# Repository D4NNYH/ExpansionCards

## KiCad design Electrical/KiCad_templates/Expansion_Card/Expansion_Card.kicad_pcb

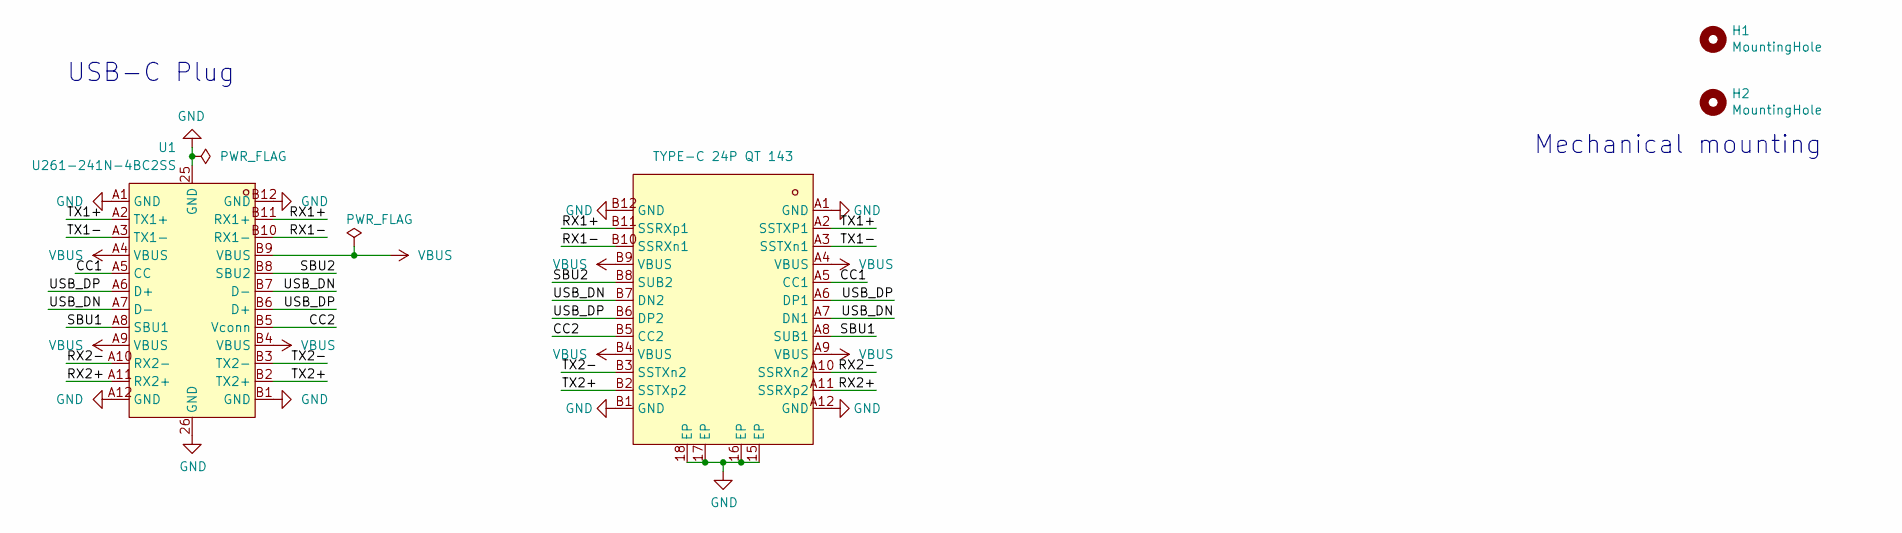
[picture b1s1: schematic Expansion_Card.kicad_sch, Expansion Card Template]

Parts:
H1, H2: MountingHole; MountingHole_2.2mm_M2
U1: U261-241N-4BC2SS; USB-C-SMD_XKB_U261-24XN-4BC2SS; MPN U261-241N-4BC2SS; LCSC Part C2938597
USB1: TYPE-C 24P QT 143; TYPE-C-SMD_C9900025773; MPN TYPE-C 24P QT 143; LCSC Part C5156605

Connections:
/CC1: U1.A5 (CC), USB1.A5 (CC1)
/CC2: U1.B5 (Vconn), USB1.B5 (CC2)
/RX1+: U1.B11 (RX1+), USB1.B11 (SSRXp1)
/RX1-: U1.B10 (RX1-), USB1.B10 (SSRXn1)
/RX2+: U1.A11 (RX2+), USB1.A11 (SSRXp2)
/RX2-: U1.A10 (RX2-), USB1.A10 (SSRXn2)
/SBU1: U1.A8 (SBU1), USB1.A8 (SUB1)
/SBU2: U1.B8 (SBU2), USB1.B8 (SUB2)
/TX1+: U1.A2 (TX1+), USB1.A2 (SSTXP1)
/TX1-: U1.A3 (TX1-), USB1.A3 (SSTXn1)
/TX2+: U1.B2 (TX2+), USB1.B2 (SSTXp2)
/TX2-: U1.B3 (TX2-), USB1.B3 (SSTXn2)
/USB_DN: U1.A7 (D-), U1.B7 (D-), USB1.A7 (DN1), USB1.B7 (DN2)
/USB_DP: U1.A6 (D+), U1.B6 (D+), USB1.A6 (DP1), USB1.B6 (DP2)
GND: U1.25 (GND), U1.26 (GND), U1.A1 (GND), U1.A12 (GND), U1.B1 (GND), U1.B12 (GND), USB1.15 (EP), USB1.16 (EP), USB1.17 (EP), USB1.18 (EP), USB1.A1 (GND), USB1.A12 (GND), USB1.B1 (GND), USB1.B12 (GND)
VBUS: U1.A4 (VBUS), U1.A9 (VBUS), U1.B4 (VBUS), U1.B9 (VBUS), USB1.A4 (VBUS), USB1.A9 (VBUS), USB1.B4 (VBUS), USB1.B9 (VBUS)

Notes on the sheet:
USB-C Plug
Mechanical mounting

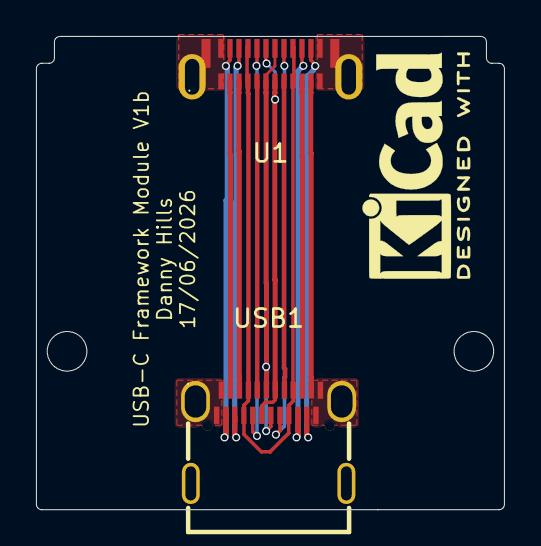
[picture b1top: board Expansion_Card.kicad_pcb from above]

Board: 4 copper layers, 26.0 x 26.3 mm, 4 parts (0 on the bottom side), 16 nets.

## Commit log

2026-06-07 Submitted for fabrication
2026-06-07 Schematic done, Currently routing
2026-06-17 Updated PCB and Re-Ordered
    + Added Local Libraries to Project
2026-06-17 Updated to use local footprint library
2026-06-17 updated library weirdness

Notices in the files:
Electrical/KiCad_templates/Expansion_Card/Expansion_Card.kicad_pcb:
This work is licensed under a Creative Commons Attribution 4.0 International License
